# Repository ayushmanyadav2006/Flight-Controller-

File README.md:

# Flight-Controller-

Created a electronic control hardware to control the roll, pitch, yaw of a airplane
Also the speed of the airplane, landing gears etc

The electronics consists of 
Arduino Uno (Microcontroller board) 
Joystick (Controlling the roll and pitch)
Potentiometer (Controlling the speed of the airplane)
Buttons (Controlling the yaw of the airplane) 
Joystick button (Controlling the landing gear) 

All the connections were made on breadboard by using jumper wires

I also made the PCB for the samne breadboard electronics.

Working video link: https://www.youtube.com/watch?v=8yyL5-LtBI4&t=84s

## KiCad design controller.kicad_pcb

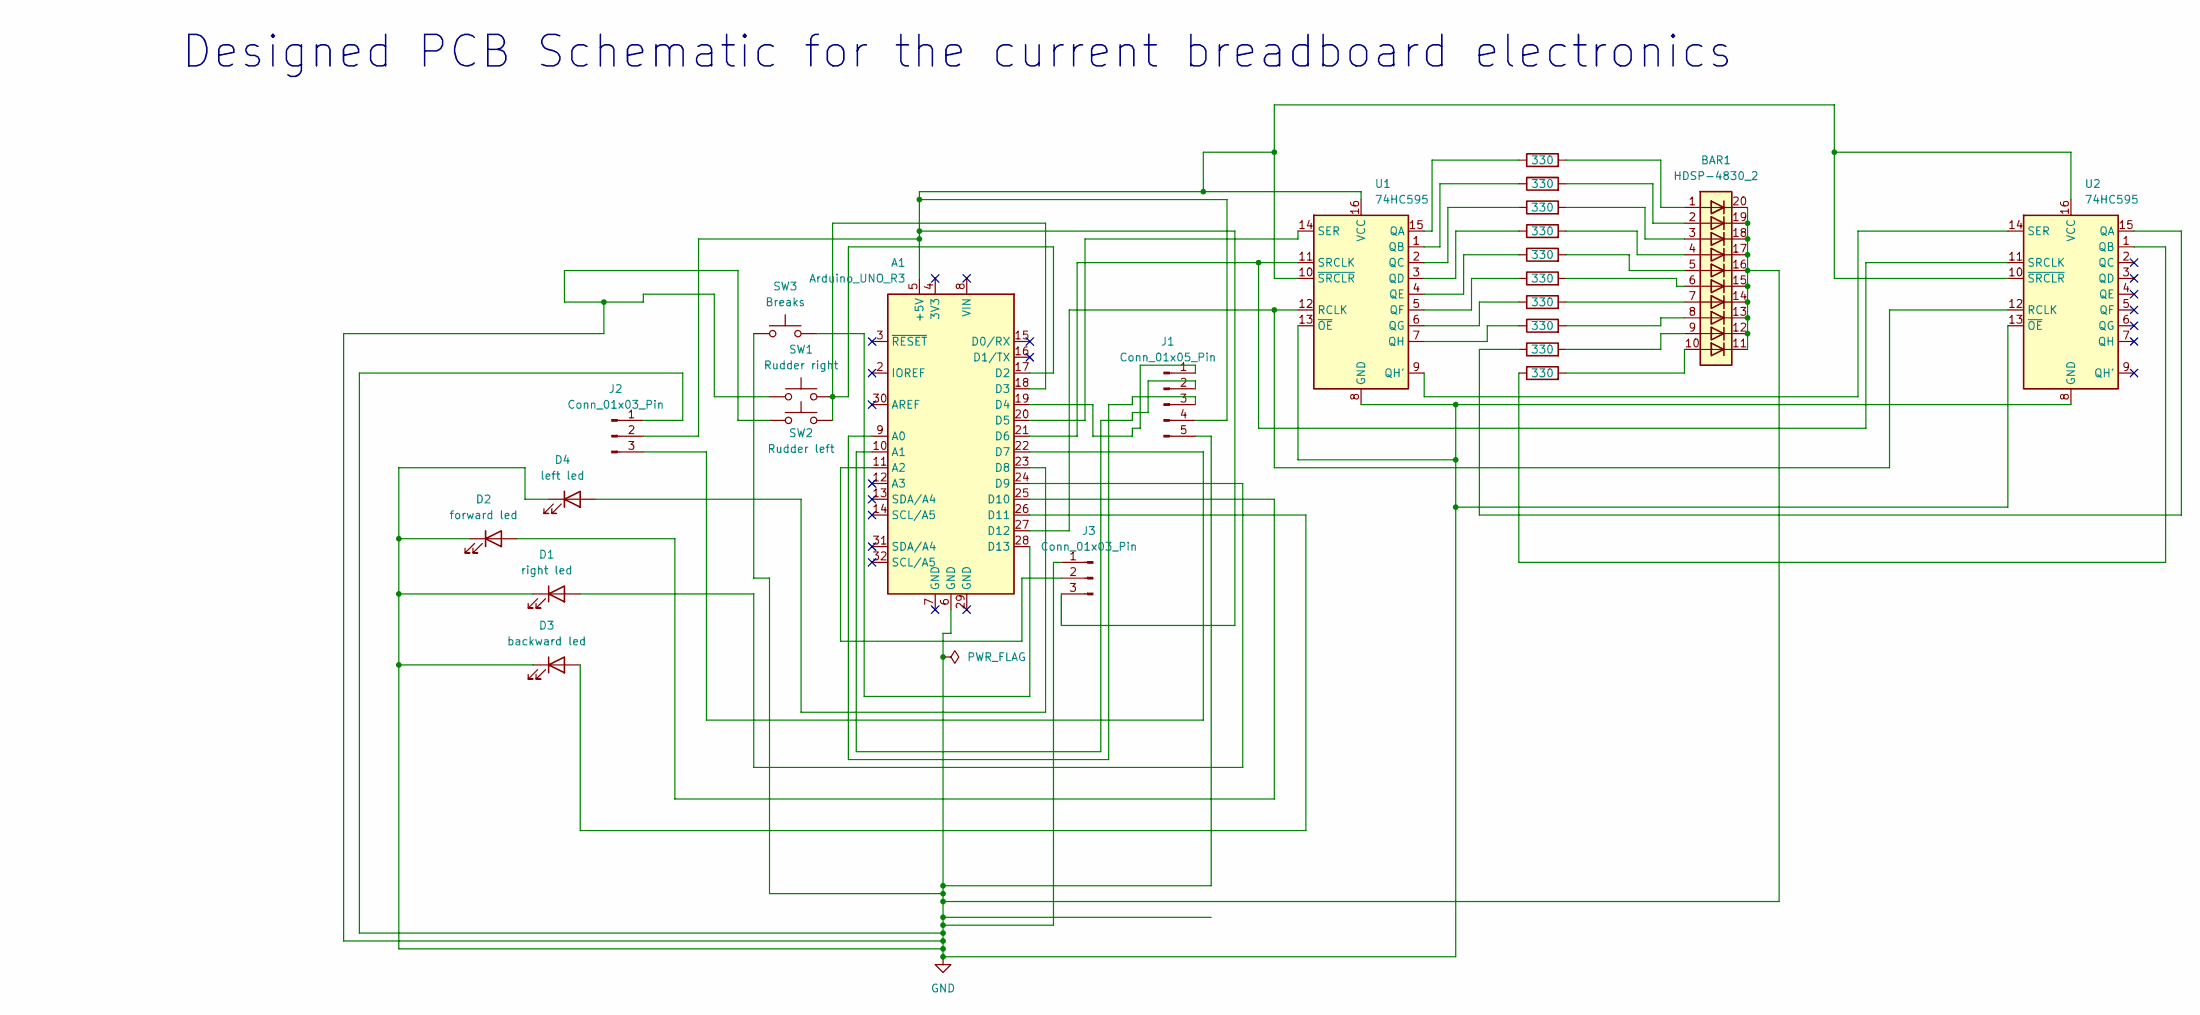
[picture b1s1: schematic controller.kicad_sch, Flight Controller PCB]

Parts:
A1: Arduino_UNO_R3
BAR1: HDSP-4830_2; HDSP-4830
D1: right led; LED_D5.0mm
D2: forward led; LED_D5.0mm
D3: backward led; LED_D5.0mm
D4: left led; LED_D5.0mm
J1: Conn_01x05_Pin; PinSocket_1x05_P2.54mm_Horizontal
J2, J3: Conn_01x03_Pin; PinHeader_1x03_P2.54mm_Vertical
R1, R2, R3, R4, R5, R6, R7, R8, R9, R10: 330; R_Axial_DIN0207_L6.3mm_D2.5mm_P7.62mm_Horizontal
SW1: Rudder right; SW_PUSH_6mm
SW2: Rudder left; SW_PUSH_6mm
SW3: Breaks; SW_PUSH_6mm
U1, U2: 74HC595; DIP-16_W7.62mm_Socket

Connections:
GND: A1.6 (GND), BAR1.11 (K), BAR1.12 (K), BAR1.13 (K), BAR1.14 (K), BAR1.15 (K), BAR1.16 (K), BAR1.17 (K), BAR1.18 (K), BAR1.19 (K), BAR1.20 (K), D1.1 (K), D2.1 (K), D3.1 (K), D4.1 (K), J1.5, J2.1, J3.1, SW1.1, SW2.1, SW3.1, U1.8 (GND), U1.13 (~OE), U2.8 (GND), U2.13 (~OE)
unnamed: A1.5 (+5V), J1.4, J2.2, J3.3, U1.10 (~SRCLR), U1.16 (VCC), U2.10 (~SRCLR), U2.16 (VCC)
unnamed: A1.9 (A0), J1.3
unnamed: A1.10 (A1), J1.2
unnamed: A1.11 (A2), J3.2
unnamed: A1.17 (D2), A1.18 (D3), SW1.2, SW2.2
unnamed: A1.19 (D4), J1.1
unnamed: A1.20 (D5), U1.14 (SER)
unnamed: A1.21 (D6), U1.11 (SRCLK), U2.11 (SRCLK)
unnamed: A1.22 (D7), J2.3
unnamed: A1.23 (D8), D4.2 (A)
unnamed: A1.24 (D9), D1.2 (A)
unnamed: A1.25 (D10), D2.2 (A)
unnamed: A1.26 (D11), D3.2 (A)
unnamed: A1.27 (D12), U1.12 (RCLK), U2.12 (RCLK)
unnamed: A1.28 (D13), SW3.2
unnamed: BAR1.1 (A), R1.2
unnamed: BAR1.2 (A), R2.2
unnamed: BAR1.3 (A), R3.2
unnamed: BAR1.4 (A), R4.2
unnamed: BAR1.5 (A), R5.2
unnamed: BAR1.6 (A), R6.2
unnamed: BAR1.7 (A), R7.2
unnamed: BAR1.8 (A), R8.2
unnamed: BAR1.9 (A), R9.2
unnamed: BAR1.10 (A), R10.2
unnamed: R1.1, U1.15 (QA)
unnamed: R2.1, U1.1 (QB)
unnamed: R3.1, U1.2 (QC)
unnamed: R4.1, U1.3 (QD)
unnamed: R5.1, U1.4 (QE)
unnamed: R6.1, U1.5 (QF)
unnamed: R7.1, U1.6 (QG)
unnamed: U1.9 (QH'), U2.14 (SER)
unnamed: R8.1, U1.7 (QH)
unnamed: R9.1, U2.15 (QA)
unnamed: R10.1, U2.1 (QB)

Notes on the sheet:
Designed PCB Schematic for the current breadboard electronics

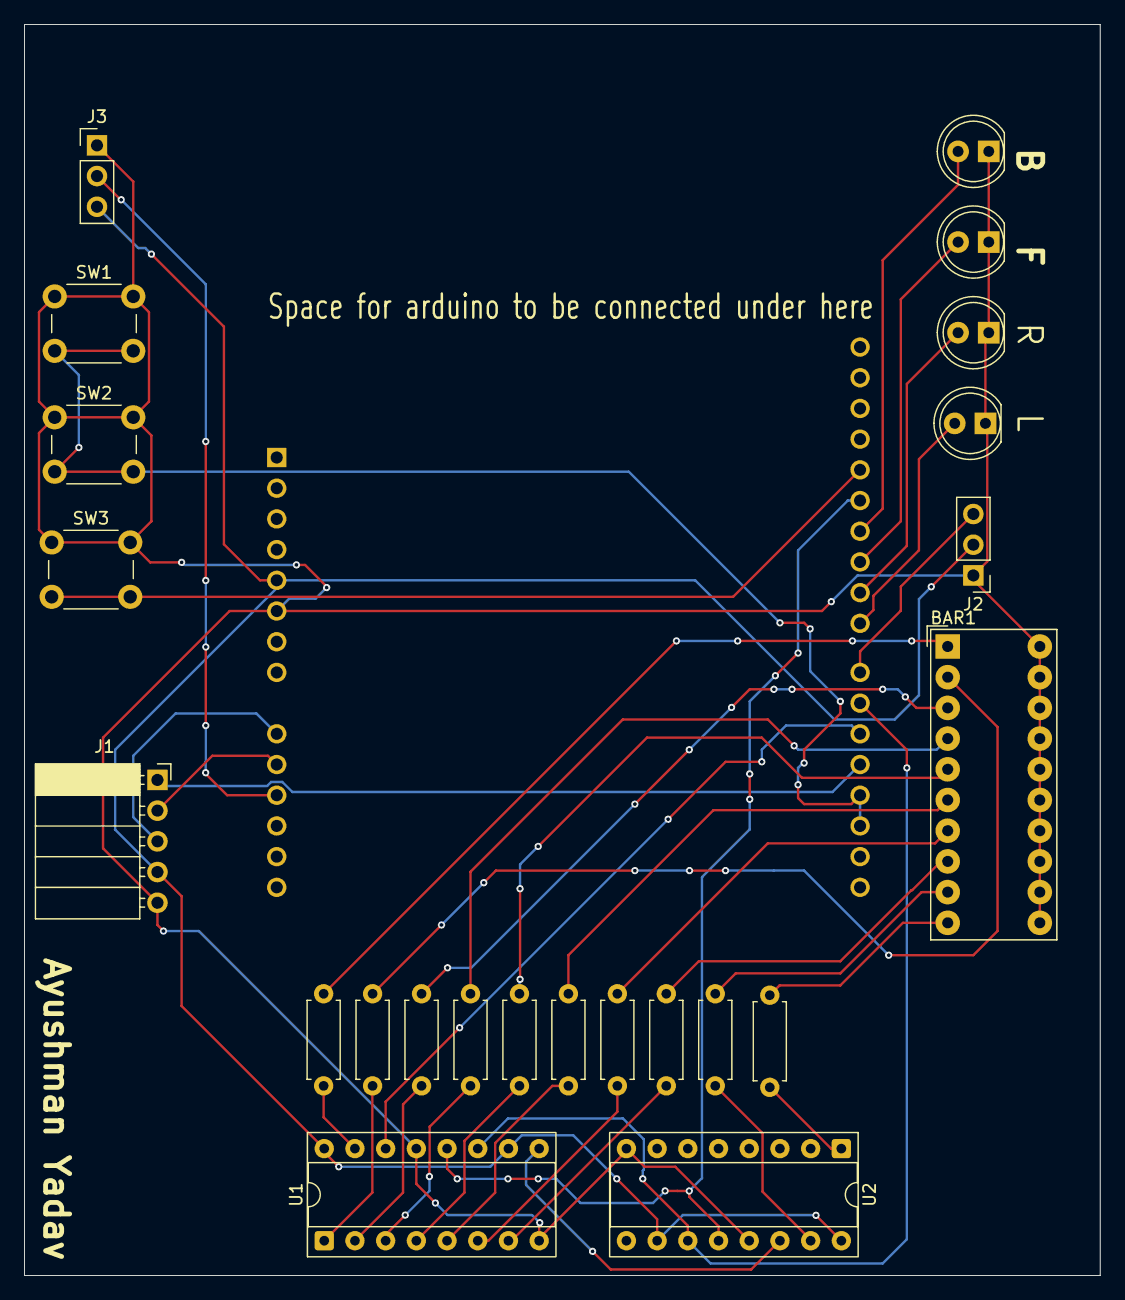
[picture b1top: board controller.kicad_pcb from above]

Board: 2 copper layers, 89.0 x 103.5 mm, 24 parts (1 on the bottom side), 37 nets.
